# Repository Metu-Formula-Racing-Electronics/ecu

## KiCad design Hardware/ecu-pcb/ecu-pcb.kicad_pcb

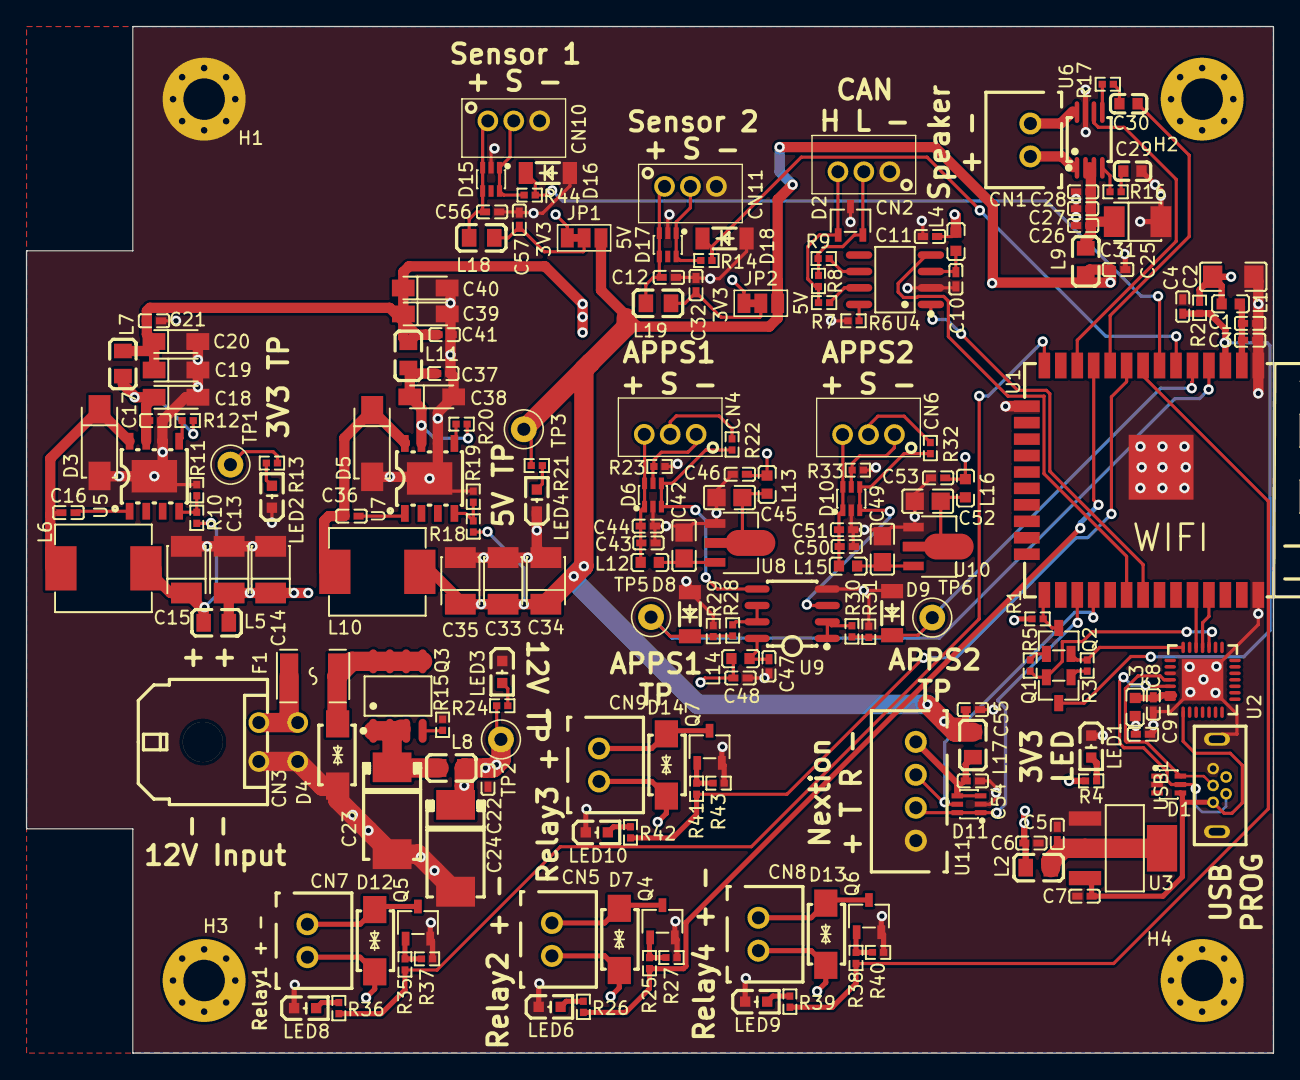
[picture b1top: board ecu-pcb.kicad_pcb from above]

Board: 4 copper layers, 96.2 x 79.2 mm, 187 parts (0 on the bottom side), 98 nets.

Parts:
C1, C5, C6, C7, C8, C10, C17, C21, C37, C41, C47, C48: 100nF; C0402_NEW
C2: 47uF; C1206
C3, C9, C11, C25, C26, C43, C44, C46, C50, C51, C53: 1uF; C0402
C4, C12, C32, C54, C55, C56, C57: 10uF; C0402
C13, C14, C15, C33, C34, C35: 100uF; CAP-SMD_L3.5-W2.8
C16, C36: 10nF; C0402
C18, C19, C20, C38, C39, C40: 10uF; CAP-SMD_L3.2-W1.6-RD-C7171
C22: 16V 100nF X7R ±10% 0402; C0402_NEW
C23, C24: 100uF; CAP-SMD_L7.3-W4.3-L-FD
C27, C28: 25V 1uF X5R ±10% 0402; C0402
C29, C30: 15nF; C0603
C31: 100uF 6.3V Tantal 3528; CAP-SMD_L3.5-W2.8
C42, C45, C49, C52: 10uF; C0805
CN1, CN5, CN7, CN8, CN9: B2B-XH-A(LF)(SN); CONN-TH_B2B-XH-A-LF-SN
CN2, CN4, CN6, CN10, CN11: B3B-PH-K-S(LF)(SN); CONN-TH_B3B-PH-K-S
CN3: 0430450400; CONN-TH_0430450400
D1, D6, D10, D11, D15, D17: SMF05CT1G; SOT-363_L2.0-W1.3-P0.65-LS2.1-BR
D2: PSM712-LF-T7; SOT-23-3_L3.0-W1.7-P0.95-LS2.9-BR
D3, D5: SS14; SMA_L4.2-W2.6-LS5.3-RD
D4, D7, D12, D13, D14: SMAJ14CA; SMA_L4.3-W2.7-LS5.1-BI
D8, D9, D16, D18: ZMM3V3; LL-34_L3.5-W1.5-RD
F1: 33V 750mA Fuse; F1812
H1, H2, H3, H4: MountingHole_3.2mm_M3_Pad_Via
JP1, JP2: SolderJumper_3_Bridged12; SolderJumper-3_P1.3mm_Bridged12_Pad1.0x1.5mm_NumberLabels
L1, L3, L4, L12, L13, L14, L15, L16: 600Ω 200mA; L0603
L2, L5, L7, L8, L9, L11, L17, L18, L19: 100Ω 800mA; L0805
L6, L10: 3A 22uH ±20% 107mΩ; IND-SMD_L7.3-W6.6
LED1, LED6, LED8, LED9, LED10: Green LED 0603; LED0603-R-RD
LED2, LED3, LED4: Red LED 0603; LED0603-R-RD
Q1, Q2: SS8050_C2150; SOT-23-3_L2.9-W1.3-P1.90-LS2.4-BR
Q3: AO4407; SOP-8_L4.9-W3.9-P1.27-LS6.0-BL
Q4, Q5, Q6, Q7: AO3400A; SOT-23-3_L2.9-W1.6-P1.90-LS2.8-BR
R1, R2, R3, R5, R28, R29, R30, R31: 10kΩ 0402 50V; R0402
R4: 4.7kΩ 0402 50V; R0402
R6, R13, R21, R23, R26, R33, R36, R39, R42: 1kΩ 0402 50V; R0402
R7, R9: 0Ω; R0402
R8: 120Ω; R0402
R10, R18: 56kΩ; R0402
R11: 33kΩ; R0402
R12, R20, R27, R37, R40, R43: 10kΩ; R0402
R14, R15, R22, R32, R44: 100Ω 0402 50V; R0402
R16, R17: 150kΩ 0402 50V; R0402
R19: 18kΩ; R0402
R24: 2.2kΩ 0402 50V; R0402
R25, R35, R38, R41: 100Ω; R0402
TP1, TP2, TP3, TP5, TP6: TestPoint; TestPoint_Loop_D2.50mm_Drill1.0mm_LowProfile
U1: ESP32-SOLO-1; WIFIM-SMD_38P-L25.5-W18.0-P1.27
U2: CP2102-GMR; WQFN-28_L5.0-W5.0-P0.50-BL-EP3.2
U3: AMS1117-3.3; SOT-223-3_L6.5-W3.4-P2.30-LS7.0-BR
U4: SN65HVD230DR; SOIC-8_L4.9-W3.9-P1.27-LS6.0-BL
U5, U7: TPS5430DDAR; ESOP-8_L4.9-W3.9-P1.27-LS6.0-TL-EP
U6: PAM8303DBSC; MSOP-8_L3.0-W3.0-P0.65-LS5.0-BL
U8, U10: HT7550; SOT-89-3_L4.5-W2.5-P1.50-LS4.2-BR
U9: LM358DR2G; SOIC-8_L5.0-W4.0-P1.27-LS6.0-BL
U11: B4B-XH-A(LF)(SN); CONN-TH_B4B-XH-A-LF-SN
USB1: U-E-M5DD-W-2; MICRO-USB-TH_U-E-M5DD-W-2

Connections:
+3.3V: C2.2, C6.2, C9.2, C11.2, C13.1, C14.1, JP1.1 (A), JP2.1 (A), L1.1, L2.2, L3.1, L4.1, L5.1, R1.2, R2.2, R4.2, R13.2, TP1.1
+5V: C25.2, C33.1, C34.1, C35.1, C55.2, JP1.3 (B), JP2.3 (B), L9.1, L10.1, L17.2, R18.2, R21.2, TP3.1
+12V: C19.1, C20.1, C21.2, C22.2, C24.1, C39.1, C40.1, C41.2, C46.2, C48.2, C53.2, CN5.1, CN7.1, CN8.1, CN9.1, D7.2, D12.2, D13.2, D14.2, L7.2, L8.2, L11.2, L13.1, L14.2, L16.1, R24.1, TP2.1
/AMP_ENABLE: U1.12 (IO27), U6.6 (~SD)
/APPS1: D9.1 (C), R30.1, R31.2, TP6.1, U1.5 (SENSOR_VN)
/APPS2: D8.1 (C), R28.1, R29.2, TP5.1, U1.4 (SENSOR_VP)
/APPS/Isolated Pot1/Apps_5v: C43.2, C44.2, CN4.3, D6.1, D6.6, L12.2
/APPS/Isolated Pot1/OUT: D6.3, D6.4, R22.1, U9.5 (2IN+)
/APPS/Isolated Pot/Apps_5v: C50.2, C51.2, CN6.3, D10.1, D10.6, L15.2
/APPS/Isolated Pot/OUT: D10.3, D10.4, R32.1, U9.3 (1IN+)
/Audio: C30.1, U1.10 (IO25)
/Audio Amp/Speaker+: CN1.2, U6.1 (OUT+)
/Audio Amp/Speaker-: CN1.1, U6.8 (OUT-)
/Audio Amp/Vin_f: C26.2, C27.2, C28.2, C31.1, L9.2, U6.2 (PVDD), U6.3 (VDD)
/CAND: U1.31 (IO19), U4.1 (D)
/CANR: U1.30 (IO18), U4.4 (R)
/ESP_EN: C4.2, Q1.3 (C), R2.1, U1.3 (EN)
/ESP_RX: U1.34 (RXD0), U2.26 (TXD)
/ESP_TX: U1.35 (TXD0), U2.25 (RXD)
/IO0: Q2.3 (C), R1.1, U1.25 (IO0)
/IO12: R35.1, R36.2, U1.14 (IO12)
/IO26: R25.1, R26.2, U1.11 (IO26)
/IO32: R38.1, R39.2, U1.8 (IO32)
/IO33: R41.1, R42.2, U1.9 (IO33)
/IO34: D18.1 (C), R14.1, U1.6 (IO34)
/IO35: D16.1 (C), R44.1, U1.7 (IO35)
/UART_RX: D11.5, U1.28 (IO17), U11.3
/UART_TX: D11.1, D11.6, U1.27 (IO16), U11.2
/USB_CP2102/D+: D1.6, U2.4 (D+), USB1.3 (D+)
/USB_CP2102/D-: D1.5, U2.5 (D-), USB1.2 (D-)
/USB_CP2102/DTR: Q2.2 (E), R3.1, U2.28 (DTR)
/USB_CP2102/RTS: Q1.2 (E), R5.1, U2.24 (RTS)
/USB_CP2102/VBUS: C7.2, D1.4, U2.8 (VBUS), U3.3 (VIN), USB1.1 (VCC)
GND: C1.1, C2.1, C3.1, C4.1, C5.1, C6.1, C7.1, C8.1, C9.1, C10.1, C11.1, C12.1, C13.2, C14.2, C15.2, C17.1, C18.2, C19.2, C20.2, C21.1, C22.1, C23.2, C24.2, C25.1, C26.1, C27.1, C28.1, C29.1, C31.2, C32.1, C33.2, C34.2, C35.2, C37.1, C38.2, C39.2, C40.2, C41.1, C42.1, C43.1, C44.1, C45.1, C46.1, C47.1, C48.1, C49.1, C50.1, C51.1, C52.1, C53.1, C54.1, C55.1, C56.1, C57.1, CN2.1, CN3.1, CN3.3, CN10.3, CN11.3, D1.2, D2.3 (K), D3.2 (A), D4.1, D5.2 (A), D6.2, D8.2 (A), D9.2 (A), D10.2, D11.2, D15.2, D16.2 (A), D17.2, D18.2 (A), H1.1, LED1.2 (C), LED2.2 (K), LED3.2 (K), LED4.2 (K), LED6.2 (C), LED8.2 (C), LED9.2 (C), LED10.2 (C), Q4.2 (S), Q5.2 (S), Q6.2 (S), Q7.2 (S), R6.2, R11.1, R15.1, R19.1, R23.1, R27.1, R29.1, R31.1, R33.1, R37.1, R40.1, R43.1, U1.1 (GND), U1.15 (GND), U1.38 (GND), U1.39 (GND), U2.3 (GND), U2.29 (EP), U3.1 (GND), U4.2 (GND), U5.6 (GND), U5.9 (PowerPAD), U6.7 (GND), U7.6 (GND), U7.9 (PowerPAD), U8.1 (GND), U9.4 (GND), U10.1 (GND), U11.1, USB1.5 (GND), USB1.6 (SHELL), USB1.7 (SHELL)
unnamed: C1.2, C3.2, L1.2, U1.2 (3V3)
unnamed: C5.2, L2.1, U3.2 (VOUT), U3.4 (VOUT)
unnamed: C8.2, L3.2, U2.6 (VDD), U2.7 (REGIN)
unnamed: C10.2, L4.2, U4.3 (VCC)
unnamed: C12.2, CN11.1, D17.3, D17.4, L19.1
unnamed: C15.1, L5.2, L6.1, R10.2
unnamed: C16.1, U5.1 (BOOT)
unnamed: C16.2, D3.1 (K), L6.2, U5.8 (PH)
unnamed: C17.2, C18.1, L7.1, R12.2, U5.7 (VIN)
unnamed: C23.1, L8.1, Q3.1 (S), Q3.2 (S), Q3.3 (S)
unnamed: C29.2, R16.1
unnamed: C30.2, R17.1
unnamed: C32.2, JP2.2 (C), L19.2
unnamed: C36.1, U7.1 (BOOT)
unnamed: C36.2, D5.1 (K), L10.2, U7.8 (PH)
unnamed: C37.2, C38.1, L11.1, R20.2, U7.7 (VIN)
unnamed: C42.2, L12.1, U8.3 (Vout)
unnamed: C45.2, L13.2, U8.2 (Vin)
unnamed: C47.2, L14.1, U9.8 (VCC)
unnamed: C49.2, L15.1, U10.3 (Vout)
unnamed: C52.2, L16.2, U10.2 (Vin)
unnamed: C54.2, D11.3, D11.4, L17.1, U11.4
unnamed: C56.2, CN10.1, D15.3, D15.4, L18.1
unnamed: C57.2, JP1.2 (C), L18.2
unnamed: CN2.2, D2.2 (A1), R8.1, R9.2
unnamed: CN2.3, D2.1 (A1), R7.1, R8.2
unnamed: CN3.2, CN3.4, F1.1
unnamed: CN4.1, D6.5, R23.2
unnamed: CN4.2, R22.2
unnamed: CN5.2, D7.1, Q4.3 (D)
unnamed: CN6.1, D10.5, R33.2
unnamed: CN6.2, R32.2
unnamed: CN7.2, D12.1, Q5.3 (D)
unnamed: CN8.2, D13.1, Q6.3 (D)
unnamed: CN9.2, D14.1, Q7.3 (D)
unnamed: CN10.2, D15.1, D15.6, R44.2
unnamed: CN11.2, D17.1, D17.6, R14.2
unnamed: D4.2, F1.2, Q3.5 (D), Q3.6 (D), Q3.7 (D), Q3.8 (D)
unnamed: LED1.1 (A), R4.1
unnamed: LED2.1 (A), R13.1
unnamed: LED3.1 (A), R24.2
unnamed: LED4.1 (A), R21.1
unnamed: LED6.1 (A), R26.1
unnamed: LED8.1 (A), R36.1
unnamed: LED9.1 (A), R39.1
unnamed: LED10.1 (A), R42.1
unnamed: Q1.1 (B), R3.2
unnamed: Q2.1 (B), R5.2
unnamed: Q3.4 (G), R15.2
unnamed: Q4.1 (G), R25.2, R27.2
unnamed: Q5.1 (G), R35.2, R37.2
unnamed: Q6.1 (G), R38.2, R40.2
unnamed: Q7.1 (G), R41.2, R43.2
unnamed: R6.1, U4.8 (RS)
unnamed: R7.2, U4.7 (CANH)
unnamed: R9.1, U4.6 (CANL)
unnamed: R10.1, R11.2, U5.4 (VSENSE)
unnamed: R12.1, U5.5 (ENA)
unnamed: R16.2, U6.4 (IN-)
unnamed: R17.2, U6.5 (IN+)
unnamed: R18.1, R19.2, U7.4 (VSENSE)
unnamed: R20.1, U7.5 (ENA)
unnamed: R28.2, U9.6 (2IN-), U9.7 (2OUT)
unnamed: R30.2, U9.1 (1OUT), U9.2 (1IN-)

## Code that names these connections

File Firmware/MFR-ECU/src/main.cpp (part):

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#include "esp_log.h"
#include <esp_task_wdt.h>

// Do NOT use GPIO 25 and 26, its used by R2DS audio (RELAY2 unusable)
//  GPIO 16 and 17 are used for Serial2
#define CAND GPIO_NUM_19
#define CANR GPIO_NUM_18
#define AMP_EN 27       // Amplifier enable pin, HIGH = ON, LOW = OFF
#define COOLING_PUMP 12 // Cooling Pump
#define COOLING_FAN1 32 // Cooling Fan 1
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  static u_int16_t apps2_max = 0;
  static u_int16_t apps1_min = 4095;
  static u_int16_t apps2_min = 4095;
  u_int16_t apps1 = analogRead(APPS1PIN);
  u_int16_t apps2 = analogRead(APPS2PIN);
  if (apps1 < apps1_min)
    apps1_min = apps1;
  if (apps2 < apps2_min)
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
void read_apps()
{
  static int apps1 = 0;
  static int apps2 = 0;
  static int diff = 0;
  static int correction = 0;
  static uint8_t apps_implausable_counter = 0;
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
  if (apps_reverse)
  {
    // apps1 = 100 - ((float)constrain(analogRead(APPS2PIN), APPS1LOW, APPS1HIGH) - APPS1LOW) / (APPS1HIGH - APPS1LOW) * 100;
    // apps2 = ((float)constrain(analogRead(APPS1PIN), APPS2LOW, APPS2HIGH) - APPS2LOW) / (APPS2HIGH - APPS2LOW) * 100;
    apps1 = analogRead(APPS2PIN);
    apps1 = constrain(apps1, APPS1LOW, APPS1HIGH);
    apps1 = map(apps1, APPS1LOW, APPS1HIGH, 0, 100);
  }
  else
  {
    // apps1 = 100 - ((float)constrain(analogRead(APPS1PIN), APPS1LOW, APPS1HIGH) - APPS1LOW) / (APPS1HIGH - APPS1LOW) * 100;
    // apps2 = ((float)constrain(analogRead(APPS2PIN), APPS2LOW, APPS2HIGH) - APPS2LOW) / (APPS2HIGH - APPS2LOW) * 100;
    apps1 = analogRead(APPS2PIN);
    apps1 = constrain(apps1, APPS1LOW, APPS1HIGH);
    apps1 = map(apps1, APPS1LOW, APPS1HIGH, 100, 0);
  }
  // apps_avg = (apps1 + apps2) / 2;
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
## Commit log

2023-03-19 Sensor kodu hazır!
2023-03-19 2.KOmmitim
2023-04-29 Added schematic
2023-05-13 apps ilk hali
2023-05-13 Can lib created
2023-05-13 Analog Değer Değişikliği
    Analog değer üst sınırı 255'ten 4095'e çekildi.
2023-05-15 Ready to drive sound
    SPIFFS kullanarak mp3 dosyalarını çalan bi sistem oluşturuldu
2023-05-15 Updated pcb
2023-05-15 Code Review
2023-05-16 Ecu SCH Ready
2023-05-17 New branch
2023-05-17 Sensors reworked, general analog sensors are written
2023-05-19 Analog sensor pin 35 is selected for test
2023-05-19 Updated Schematic
2023-05-20 Set & read data features added
    functions to write data by directly using integer and read the data as integer from data buffer added. Data are written and read using little endian (low bit first).
    CANmsg member function write data changed to set data, which sets _data buffer via another data array
2023-05-20 working code
    mp3 is working
2023-05-25 PCB Done
2023-05-26 Added Vertical USB
2023-06-07 can now play 2 mp3 files
2023-06-07 datalog ilk commit
    deneme
2023-06-07 sdasda
    s
2023-06-07 Latest HW
2023-06-07 Apps Son
    APPS SON HAli
2023-06-18 kayıt 3
2023-06-21 Bamocar can library
    can.attach function at bamocar_can.h is to be discussed, as well as soft and hard enable states.
2023-06-24 Included a txt with example commands for speed control
2023-06-24 changed _parsemessage to parsemessage
2023-06-25 With changed pin
    Değiştirilmiş pin numaraları yazılkdı ancak max değer kaç olduğu unutuldu
2023-07-06 Latest
2023-07-06 hvjv
2023-07-08 updated master
2023-07-08 updated latest
2023-07-08 Added apps reverse connection
2023-07-08 comment4ed unused code
2023-07-09 Clanup
2023-07-11 sonkod
